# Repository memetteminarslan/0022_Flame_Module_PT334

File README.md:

# 0022_Flame_Module_PT334

You are seeing a large number of widely used PT334 in electronic development kits. More information coming soon...

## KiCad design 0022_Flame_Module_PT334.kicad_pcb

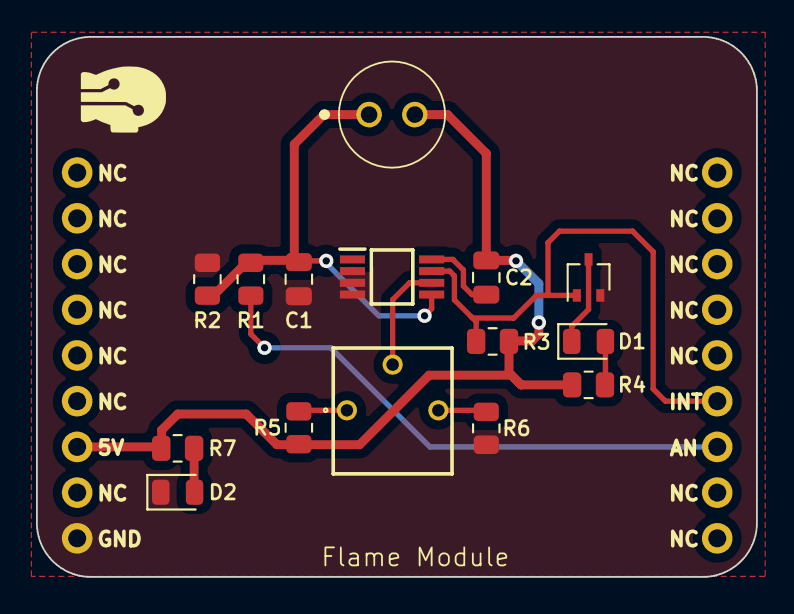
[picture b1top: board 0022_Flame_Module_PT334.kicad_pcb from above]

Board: 2 copper layers, 40.0 x 30.0 mm, 16 parts (0 on the bottom side), 12 nets.

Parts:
C1: 10nF; C_0805_2012Metric
C2: 2.2uF; C_0805_2012Metric
D1, D2: LED; LED_0805_2012Metric
IC1: LM2903BHQDGKRQ1; SOP65P490X110-8N
Q2: PDTC114EU,115; SOT-323_SC-70
Q3: PT334-6B; PT3346B
R1: 3k3; R_0805_2012Metric
R2: 6k8; R_0805_2012Metric
R3, R4: 4k7; R_0805_2012Metric
R5, R6: 5k1; R_0805_2012Metric
R7: 1k; R_0805_2012Metric
RV1: R_Potentiometer_Trim; 3362P_1
U1: pin_header

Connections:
+5V: C2.1, Q3.2 (C), R3.1, R4.1, R5.1, R7.1, U1.7
AN: R1.1, U1.12
GND: C1.2, D2.1 (K), IC1.2 (1IN-), IC1.3 (1IN+), IC1.4 (GND), Q2.2 (E), R2.2, R6.2, U1.9
IN+: C1.1, IC1.5 (2IN+), Q3.1 (E), R1.2, R2.1
IN-: IC1.6 (2IN-), RV1.2
INT: IC1.7 (2OUT), Q2.1 (B), R3.2, U1.13
unnamed: D1.2 (A), R4.2
unnamed: D1.1 (K), Q2.3 (C)
unnamed: D2.2 (A), R7.2
unnamed: C2.2, IC1.8 (VCC)
unnamed: R5.2, RV1.1
unnamed: R6.1, RV1.3
